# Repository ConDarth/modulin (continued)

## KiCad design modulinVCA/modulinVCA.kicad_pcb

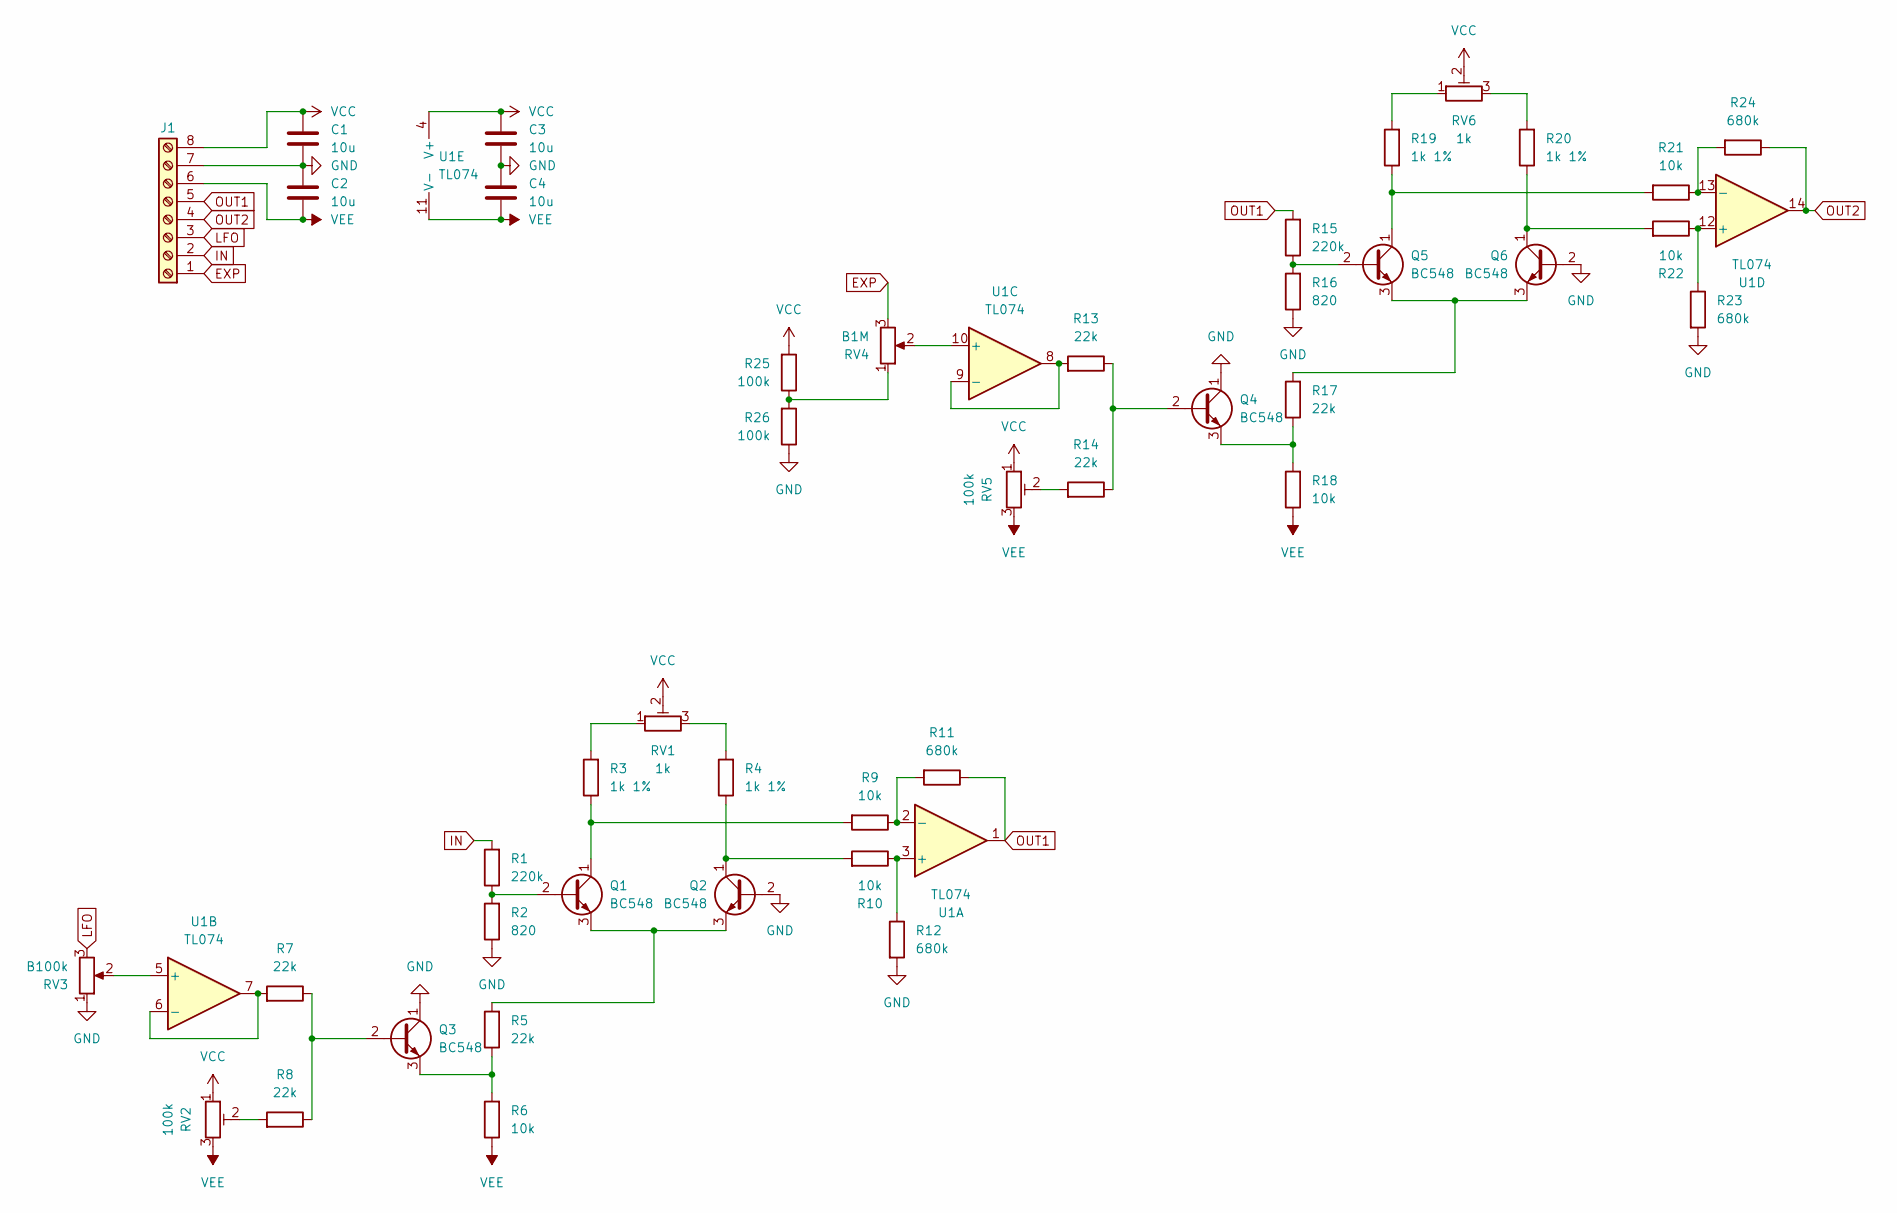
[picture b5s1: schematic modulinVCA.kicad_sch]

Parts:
C1, C2, C3, C4: 10u; C_Axial_P5.00mm_CNC
J1: Screw_Terminal_01x08; TerminalBlock_1x8_CNC
Q1, Q2, Q3, Q4, Q5, Q6: BC548; TO-92_CNC
R1, R15: 220k; R_2.54mm_CNC
R2: 820; R_2.54mm_CNC
R3, R20: 1k 1%; R_7.62mm_CNC
R4, R19: 1k 1%; R_2.54mm_CNC
R5, R17: 22k; R_10.16mm_CNC
R6, R18: 10k; R_2.54mm_CNC_Alt
R7, R13: 22k; R_5.08mm_CNC
R8, R14: 22k; R_2.54mm_CNC
R9: 10k; R_10.16mm_CNC
R10, R22: 10k; R_2.54mm_CNC
R11, R24: 680k; R_2.54mm_CNC
R12, R23: 680k; R_5.08mm_CNC
R16: 820; R_2.54mm_CNC_Alt
R21: 10k; R_7.62mm_CNC
R25, R26: 100k; R_10.16mm_CNC
RV1, RV6: 1k; Potentiometer_Trim_CNC
RV2, RV5: 100k; Potentiometer_Trim_CNC
RV3: B100k; Potentiometer_PanelMount_CNC
RV4: B1M; Potentiometer_PanelMount_CNC
U1: TL074; DIP-14_CNC

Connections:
EXP: J1.1, RV4.3
GND: C1.2, C2.1, C3.2, C4.1, J1.7, Q2.2 (B), Q3.1 (C), Q4.1 (C), Q6.2 (B), R2.1, R12.2, R16.1, R23.2, R26.1, RV3.1
IN: J1.2, R1.2
LFO: J1.3, RV3.3
unnamed: Q1.2 (B), R1.1, R2.2
unnamed: Q1.1 (C), R3.1, R9.2
unnamed: Q1.3 (E), Q2.3 (E), R5.2
unnamed: Q2.1 (C), R4.1, R10.2
unnamed: Q3.2 (B), R7.1, R8.1
unnamed: Q3.3 (E), R5.1, R6.2
unnamed: Q4.2 (B), R13.1, R14.1
unnamed: Q4.3 (E), R17.1, R18.2
unnamed: Q5.2 (B), R15.1, R16.2
unnamed: Q5.1 (C), R19.1, R21.2
unnamed: Q5.3 (E), Q6.3 (E), R17.2
unnamed: Q6.1 (C), R20.1, R22.2
unnamed: R3.2, RV1.1
unnamed: R4.2, RV1.3
unnamed: R8.2, RV2.2
unnamed: R14.2, RV5.2
unnamed: R19.2, RV6.1
unnamed: R20.2, RV6.3
unnamed: R25.1, R26.2, RV4.1
unnamed: R10.1, R12.1, U1.3 (+)
unnamed: R9.1, R11.2, U1.2 (-)
unnamed: RV3.2, U1.5 (+)
unnamed: R7.2, U1.6 (-), U1.7
unnamed: RV4.2, U1.10 (+)
unnamed: R13.2, U1.8, U1.9 (-)
unnamed: R22.1, R23.1, U1.12 (+)
unnamed: R21.1, R24.2, U1.13 (-)
OUT1: J1.5, R11.1, R15.2, U1.1
OUT2: J1.4, R24.1, U1.14
VCC: C1.1, C3.1, J1.8, R25.2, RV1.2, RV2.1, RV5.1, RV6.2, U1.4 (V+)
VEE: C2.2, C4.2, J1.6, R6.1, R18.1, RV2.3, RV5.3, U1.11 (V-)

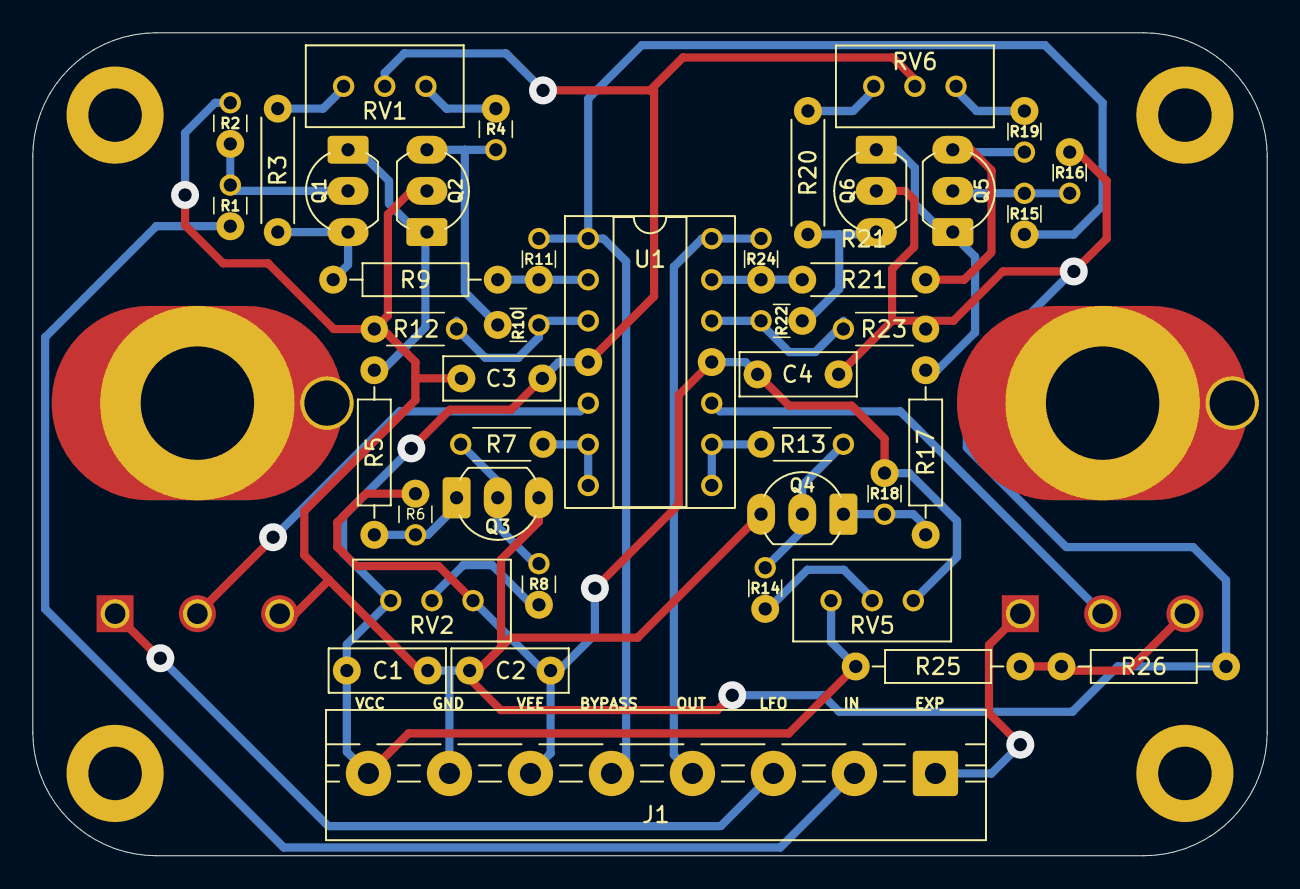
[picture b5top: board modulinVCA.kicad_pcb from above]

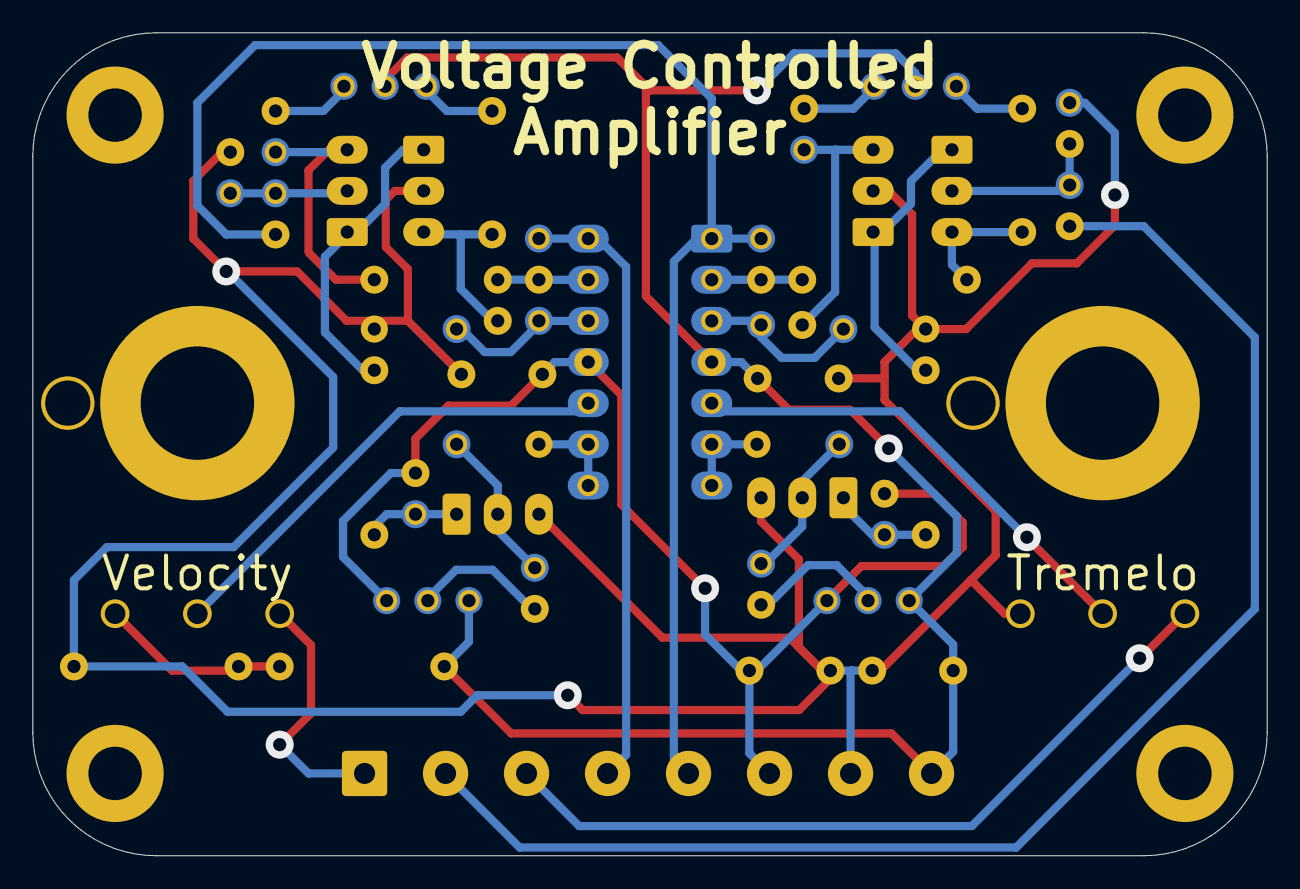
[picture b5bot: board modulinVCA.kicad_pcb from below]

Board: 2 copper layers, 76.2 x 50.8 mm, 44 parts (2 on the bottom side), 35 nets.

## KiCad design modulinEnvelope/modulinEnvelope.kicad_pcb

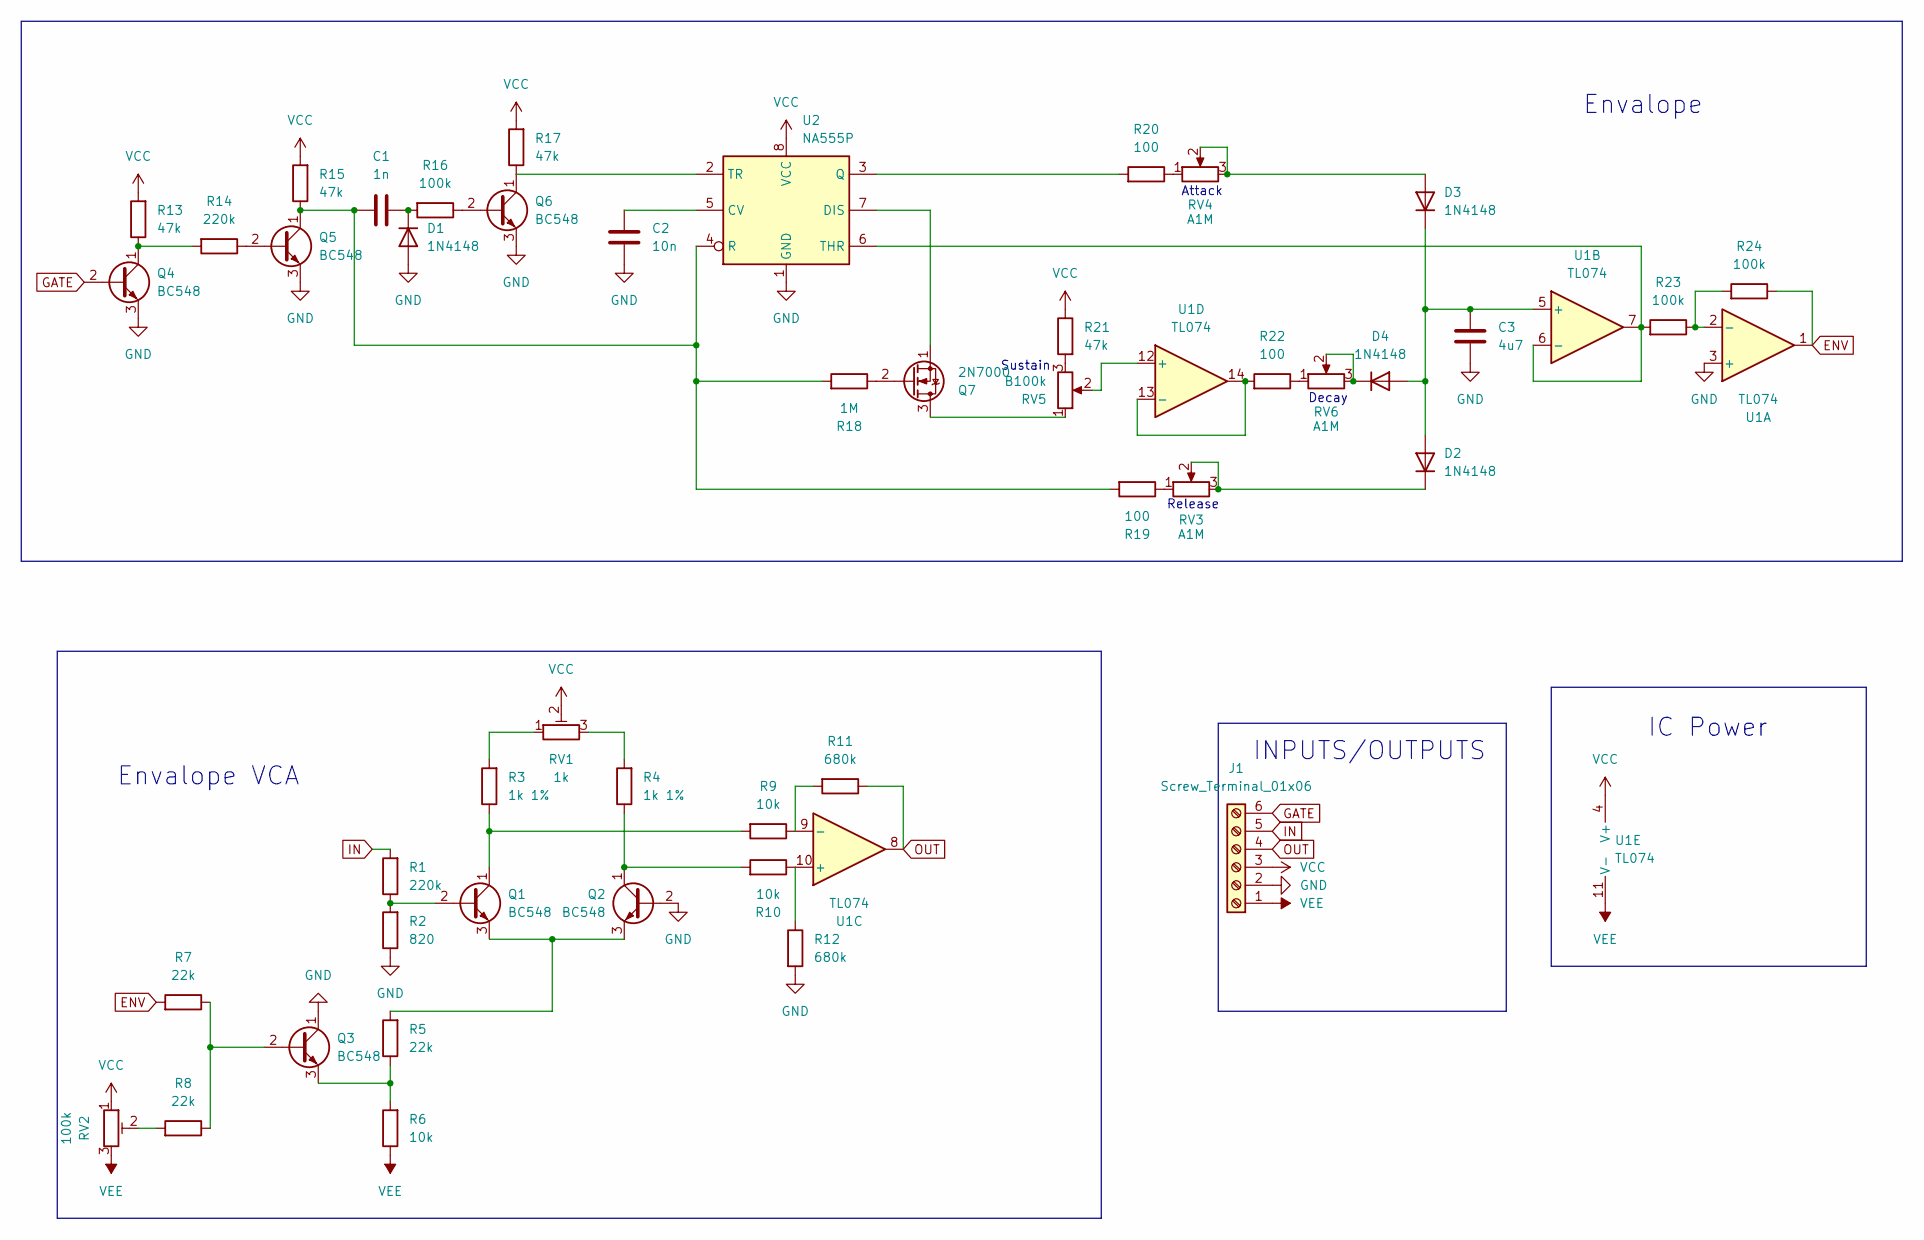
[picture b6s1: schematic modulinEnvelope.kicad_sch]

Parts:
C1: 1n; C_Rect_P5.00mm_CNC
C2: 10n; C_Rect_P5.00mm_CNC
C3: 4u7; C_Rect_P5.00mm_CNC
D1: 1N4148; D_P7.62mm_CNC
D2, D3, D4: 1N4148; D_P10.16mm_CNC
J1: Screw_Terminal_01x06; TerminalBlock_1x6_CNC
Q1, Q2, Q3, Q4, Q5, Q6: BC548; TO-92_CNC
Q7: 2N7000; TO-92_CNC
R1: 220k; R_10.16mm_CNC
R2: 820; R_10.16mm_CNC
R3: 1k 1%; R_7.62mm_CNC
R4: 1k 1%; R_2.54mm_CNC
R5, R7, R8: 22k; R_10.16mm_CNC
R6, R9, R10: 10k; R_10.16mm_CNC
R11: 680k; R_7.62mm_CNC
R12: 680k; R_10.16mm_CNC
R13, R15, R17: 47k; R_7.62mm_CNC
R14: 220k; R_7.62mm_CNC
R16, R23, R24: 100k; R_7.62mm_CNC
R18: 1M; R_7.62mm_CNC
R19, R20, R22: 100; R_10.16mm_CNC
R21: 47k; R_10.16mm_CNC
RV1: 1k; Potentiometer_Trim_CNC
RV2: 100k; Potentiometer_Trim_CNC
RV3, RV4, RV6: A1M; Potentiometer_PanelMount_CNC
RV5: B100k; Potentiometer_PanelMount_CNC
U1: TL074; DIP-14_CNC
U2: NA555P; DIP-8_CNC

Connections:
ENV: R7.2, R24.1, U1.1
GATE: J1.6, Q4.2 (B)
GND: C2.1, C3.1, D1.2 (A), J1.2, Q2.2 (B), Q3.1 (C), Q4.3 (E), Q5.3 (E), Q6.3 (E), R2.1, R12.2, U1.3 (+), U2.1 (GND)
IN: J1.5, R1.2
unnamed: C1.2, D1.1 (K), R16.2
unnamed: C3.2, D2.2 (A), D3.1 (K), D4.2 (A), U1.5 (+)
unnamed: D2.1 (K), RV3.2, RV3.3
unnamed: D3.2 (A), RV4.2, RV4.3
unnamed: D4.1 (K), RV6.2, RV6.3
unnamed: Q1.2 (B), R1.1, R2.2
unnamed: Q1.1 (C), R3.1, R9.2
unnamed: Q1.3 (E), Q2.3 (E), R5.2
unnamed: Q2.1 (C), R4.1, R10.2
unnamed: Q3.2 (B), R7.1, R8.1
unnamed: Q3.3 (E), R5.1, R6.2
unnamed: Q4.1 (C), R13.1, R14.2
unnamed: Q5.2 (B), R14.1
unnamed: C1.1, Q5.1 (C), R15.1, R18.2, R19.2, U2.4 (R)
unnamed: Q6.2 (B), R16.1
unnamed: Q6.1 (C), R17.1, U2.2 (TR)
unnamed: Q7.3 (D), RV5.1
unnamed: Q7.2 (G), R18.1
unnamed: Q7.1 (S), U2.7 (DIS)
unnamed: R3.2, RV1.1
unnamed: R4.2, RV1.3
unnamed: R8.2, RV2.2
unnamed: R19.1, RV3.1
unnamed: R20.1, RV4.1
unnamed: R21.2, RV5.3
unnamed: R22.1, RV6.1
unnamed: R23.1, R24.2, U1.2 (-)
unnamed: R23.2, U1.6 (-), U1.7, U2.6 (THR)
unnamed: R10.1, R12.1, U1.10 (+)
unnamed: R9.1, R11.2, U1.9 (-)
unnamed: RV5.2, U1.12 (+)
unnamed: R22.2, U1.13 (-), U1.14
unnamed: C2.2, U2.5 (CV)
unnamed: R20.2, U2.3 (Q)
OUT: J1.4, R11.1, U1.8
VCC: J1.3, R13.2, R15.2, R17.2, R21.1, RV1.2, RV2.1, U1.4 (V+), U2.8 (VCC)
VEE: J1.1, R6.1, RV2.3, U1.11 (V-)

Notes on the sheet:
Envalope
Envalope VCA
IC Power
Decay
INPUTS/OUTPUTS
Attack
Release
Sustain

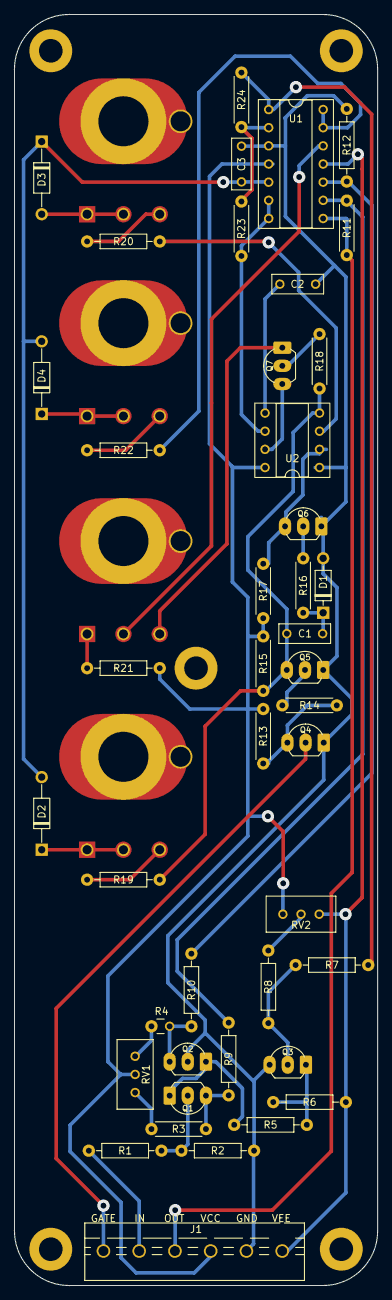
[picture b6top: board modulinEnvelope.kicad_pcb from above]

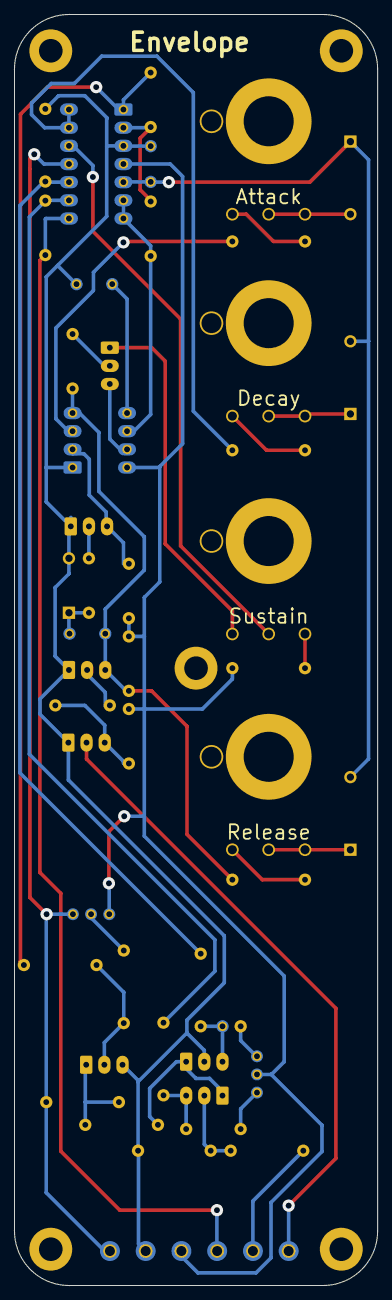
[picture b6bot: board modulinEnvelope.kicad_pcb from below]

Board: 2 copper layers, 50.8 x 177.8 mm, 47 parts (4 on the bottom side), 41 nets.

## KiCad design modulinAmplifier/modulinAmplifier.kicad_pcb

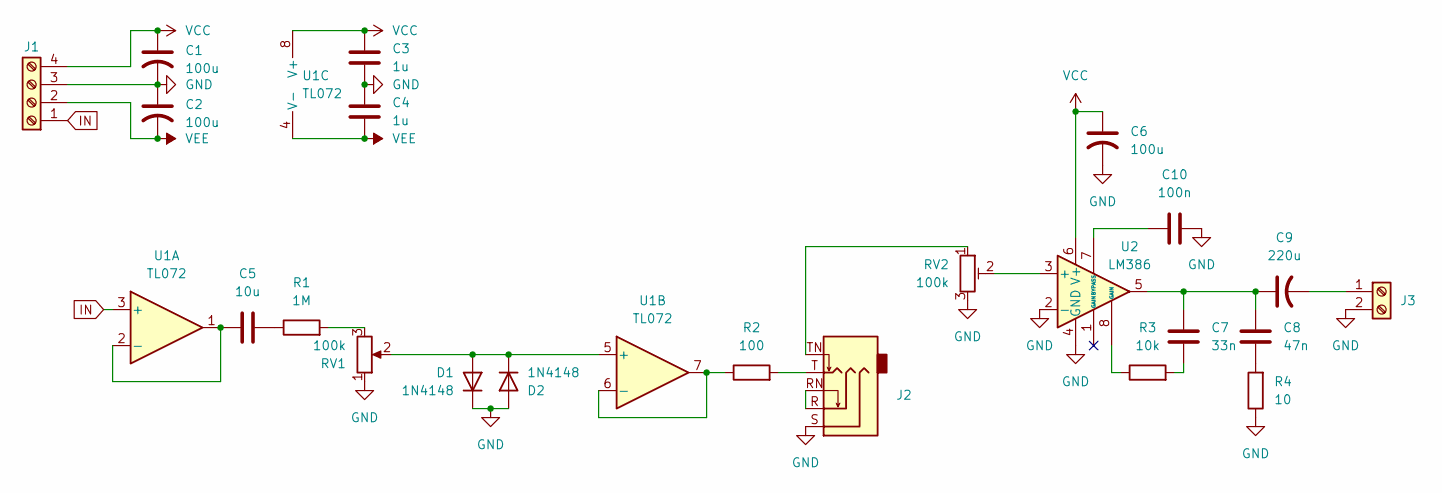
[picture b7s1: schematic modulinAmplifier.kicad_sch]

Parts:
C1, C2, C6: 100u; C_Radial_Polarized_P3.8mm_CNC
C3, C4: 1u; C_Axial_P5.00mm_CNC
C5: 10u; C_Axial_P5.00mm_CNC
C7: 33n; C_Axial_P5.00mm_CNC
C8: 47n; C_Axial_P5.00mm_CNC
C9: 220u; C_Radial_Polarized_P3.8mm_CNC
C10: 100n; C_Axial_P5.00mm_CNC
D1, D2: 1N4148; D_P7.62mm_CNC
J1: Screw_Terminal_01x04; TerminalBlock_1x4_CNC
J2: AudioJack3_SwitchTR; Jack_3.5mm_CUI_SJ1-3525N_Horizontal
J3: Screw_Terminal_01x02; TerminalBlock_1x2_CNC
R1: 1M; R_10.16mm_CNC
R2: 100; R_10.16mm_CNC
R3: 10k; R_7.62mm_CNC
R4: 10; R_10.16mm_CNC
RV1: 100k; Potentiometer_PanelMount_CNC
RV2: 100k; Potentiometer_Trim_CNC
U1: TL072; DIP-8_CNC
U2: LM386; DIP-8_CNC

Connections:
GND: C1.2, C2.1, C3.2, C4.1, C6.2, C10.1, D1.1 (K), D2.2 (A), J1.3, J2.S, J3.2, R4.1, RV1.1, RV2.3, U2.2 (-), U2.4 (GND)
IN: J1.1, U1.3 (+)
unnamed: C5.2, R1.1
unnamed: C7.1, R3.2
unnamed: C7.2, C8.2, C9.1, U2.5
unnamed: C8.1, R4.2
unnamed: D1.2 (A), D2.1 (K), RV1.2, U1.5 (+)
unnamed: J2.R, J2.RN
unnamed: J2.T, R2.2
unnamed: J2.TN, RV2.1
unnamed: C9.2, J3.1
unnamed: R1.2, RV1.3
unnamed: R3.1, U2.8 (GAIN)
unnamed: C5.1, U1.1, U1.2 (-)
unnamed: R2.1, U1.6 (-), U1.7
unnamed: RV2.2, U2.3 (+)
unnamed: C10.2, U2.7 (BYPASS)
VCC: C1.1, C3.1, C6.1, J1.4, U1.8 (V+), U2.6 (V+)
VEE: C2.2, C4.2, J1.2, U1.4 (V-)

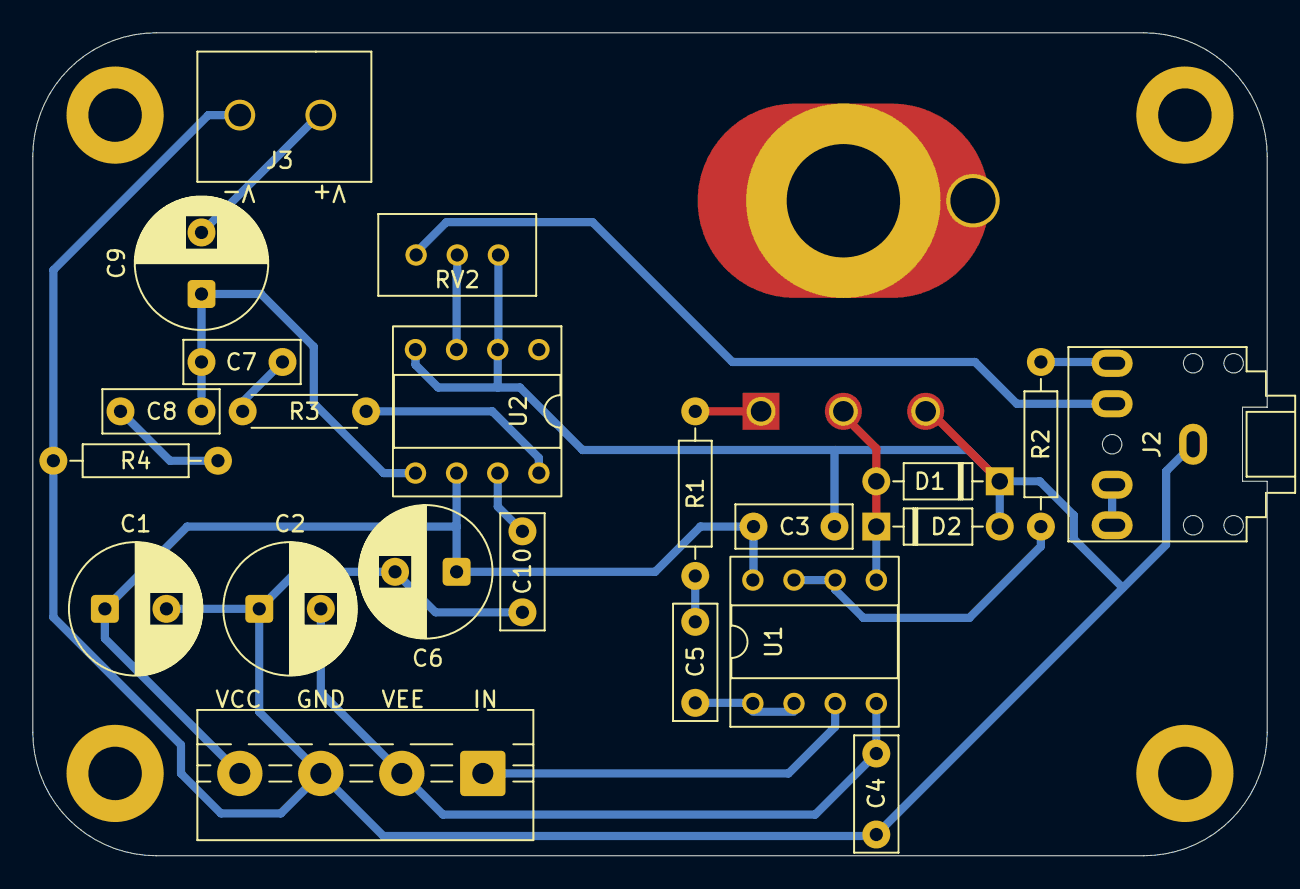
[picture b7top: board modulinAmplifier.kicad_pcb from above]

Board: 2 copper layers, 76.2 x 50.8 mm, 23 parts (1 on the bottom side), 19 nets.

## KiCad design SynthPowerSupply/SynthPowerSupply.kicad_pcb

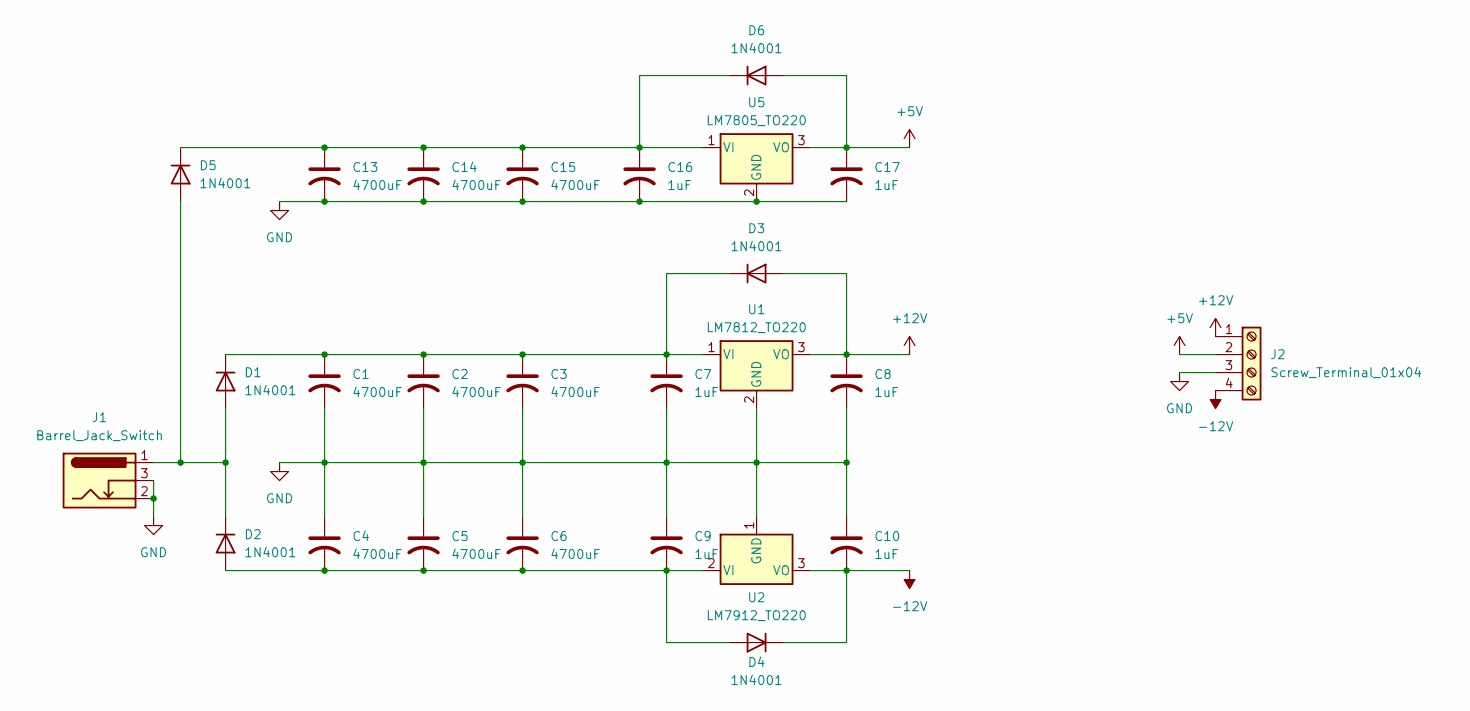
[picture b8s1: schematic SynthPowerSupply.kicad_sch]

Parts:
C1, C2, C3, C4, C5, C6, C13, C14, C15: 4700uF; CP_Radial_D16.0mm_P7.50mm
C7, C8, C9, C10, C16, C17: 1uF; CP_Radial_D4.0mm_P2.00mm
D1, D2, D3, D4, D5, D6: 1N4001; D_DO-41_SOD81_P10.16mm_Horizontal
J1: Barrel_Jack_Switch; BarrelJack_Horizontal
J2: Screw_Terminal_01x04; TerminalBlock_Xinya_XY308-2.54-4P_1x04_P2.54mm_Horizontal
U1: LM7812_TO220; TO-220-3_Vertical
U2: LM7912_TO220; TO-220-3_Vertical
U5: LM7805_TO220; TO-220-3_Vertical

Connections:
+5V: C17.1, D6.2 (A), J2.2, U5.3 (VO)
+12V: C8.1, D3.2 (A), J2.1, U1.3 (VO)
-12V: C10.2, D4.1 (K), J2.4, U2.3 (VO)
GND: C1.2, C2.2, C3.2, C4.1, C5.1, C6.1, C7.2, C8.2, C9.1, C10.1, C13.2, C14.2, C15.2, C16.2, C17.2, J1.2, J1.3, J2.3, U1.2 (GND), U2.1 (GND), U5.2 (GND)
unnamed: D1.2 (A), D2.1 (K), D5.2 (A), J1.1
unnamed: C1.1, C2.1, C3.1, C7.1, D1.1 (K), D3.1 (K), U1.1 (VI)
unnamed: C4.2, C5.2, C6.2, C9.2, D2.2 (A), D4.2 (A), U2.2 (VI)
unnamed: C13.1, C14.1, C15.1, C16.1, D5.1 (K), D6.1 (K), U5.1 (VI)

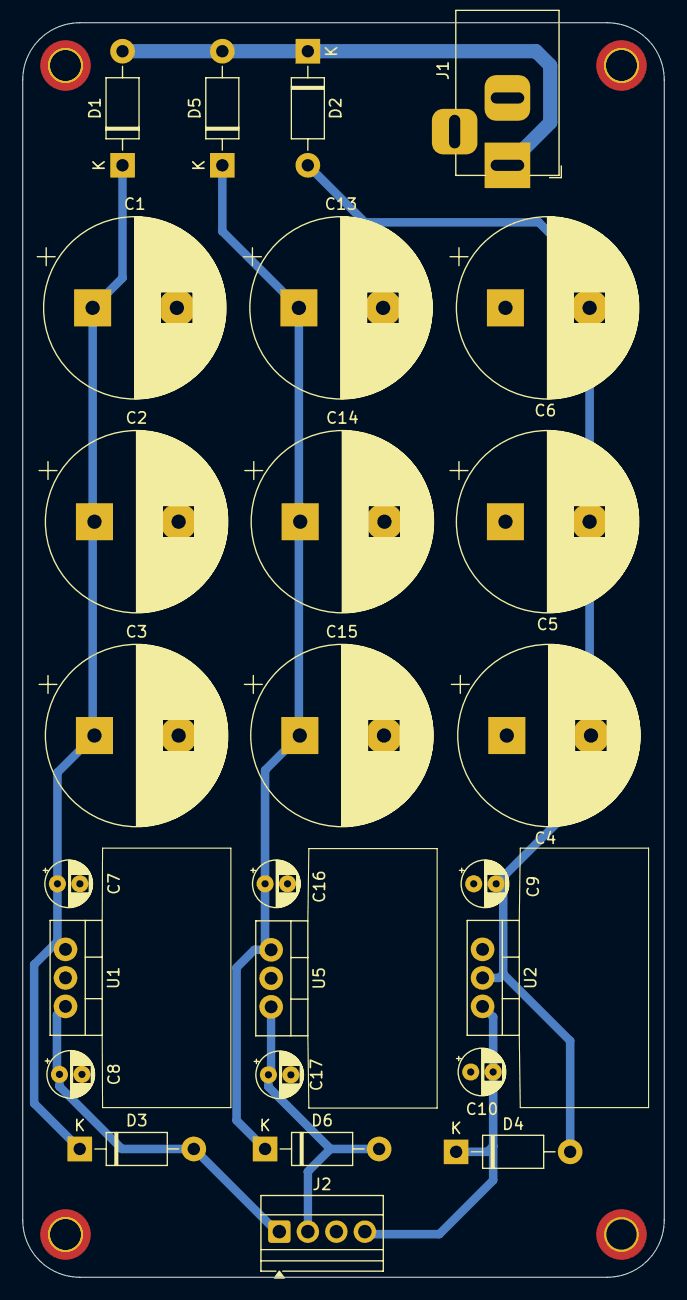
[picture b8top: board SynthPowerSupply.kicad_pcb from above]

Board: 2 copper layers, 57.1 x 111.8 mm, 26 parts (0 on the bottom side), 8 nets.

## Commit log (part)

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2025-05-07 Create Schematic
2025-05-12 Add power schematic
2025-05-14 Create Power supply PCB
2025-06-05 Edit powersupply pcb
2025-11-10 Start OCB design for parts
2025-11-13 Write out envelope circuit and make PCB, edit PSU
2025-11-13 Start Readme
2025-11-19 Finish VCO PCB
2026-03-09 Finished up LFO PCB
2026-04-22 Add VCF ciruit and edit for JLCPCB
2026-04-24 Add STEP files
2026-05-06 Add modulin BOM csv
